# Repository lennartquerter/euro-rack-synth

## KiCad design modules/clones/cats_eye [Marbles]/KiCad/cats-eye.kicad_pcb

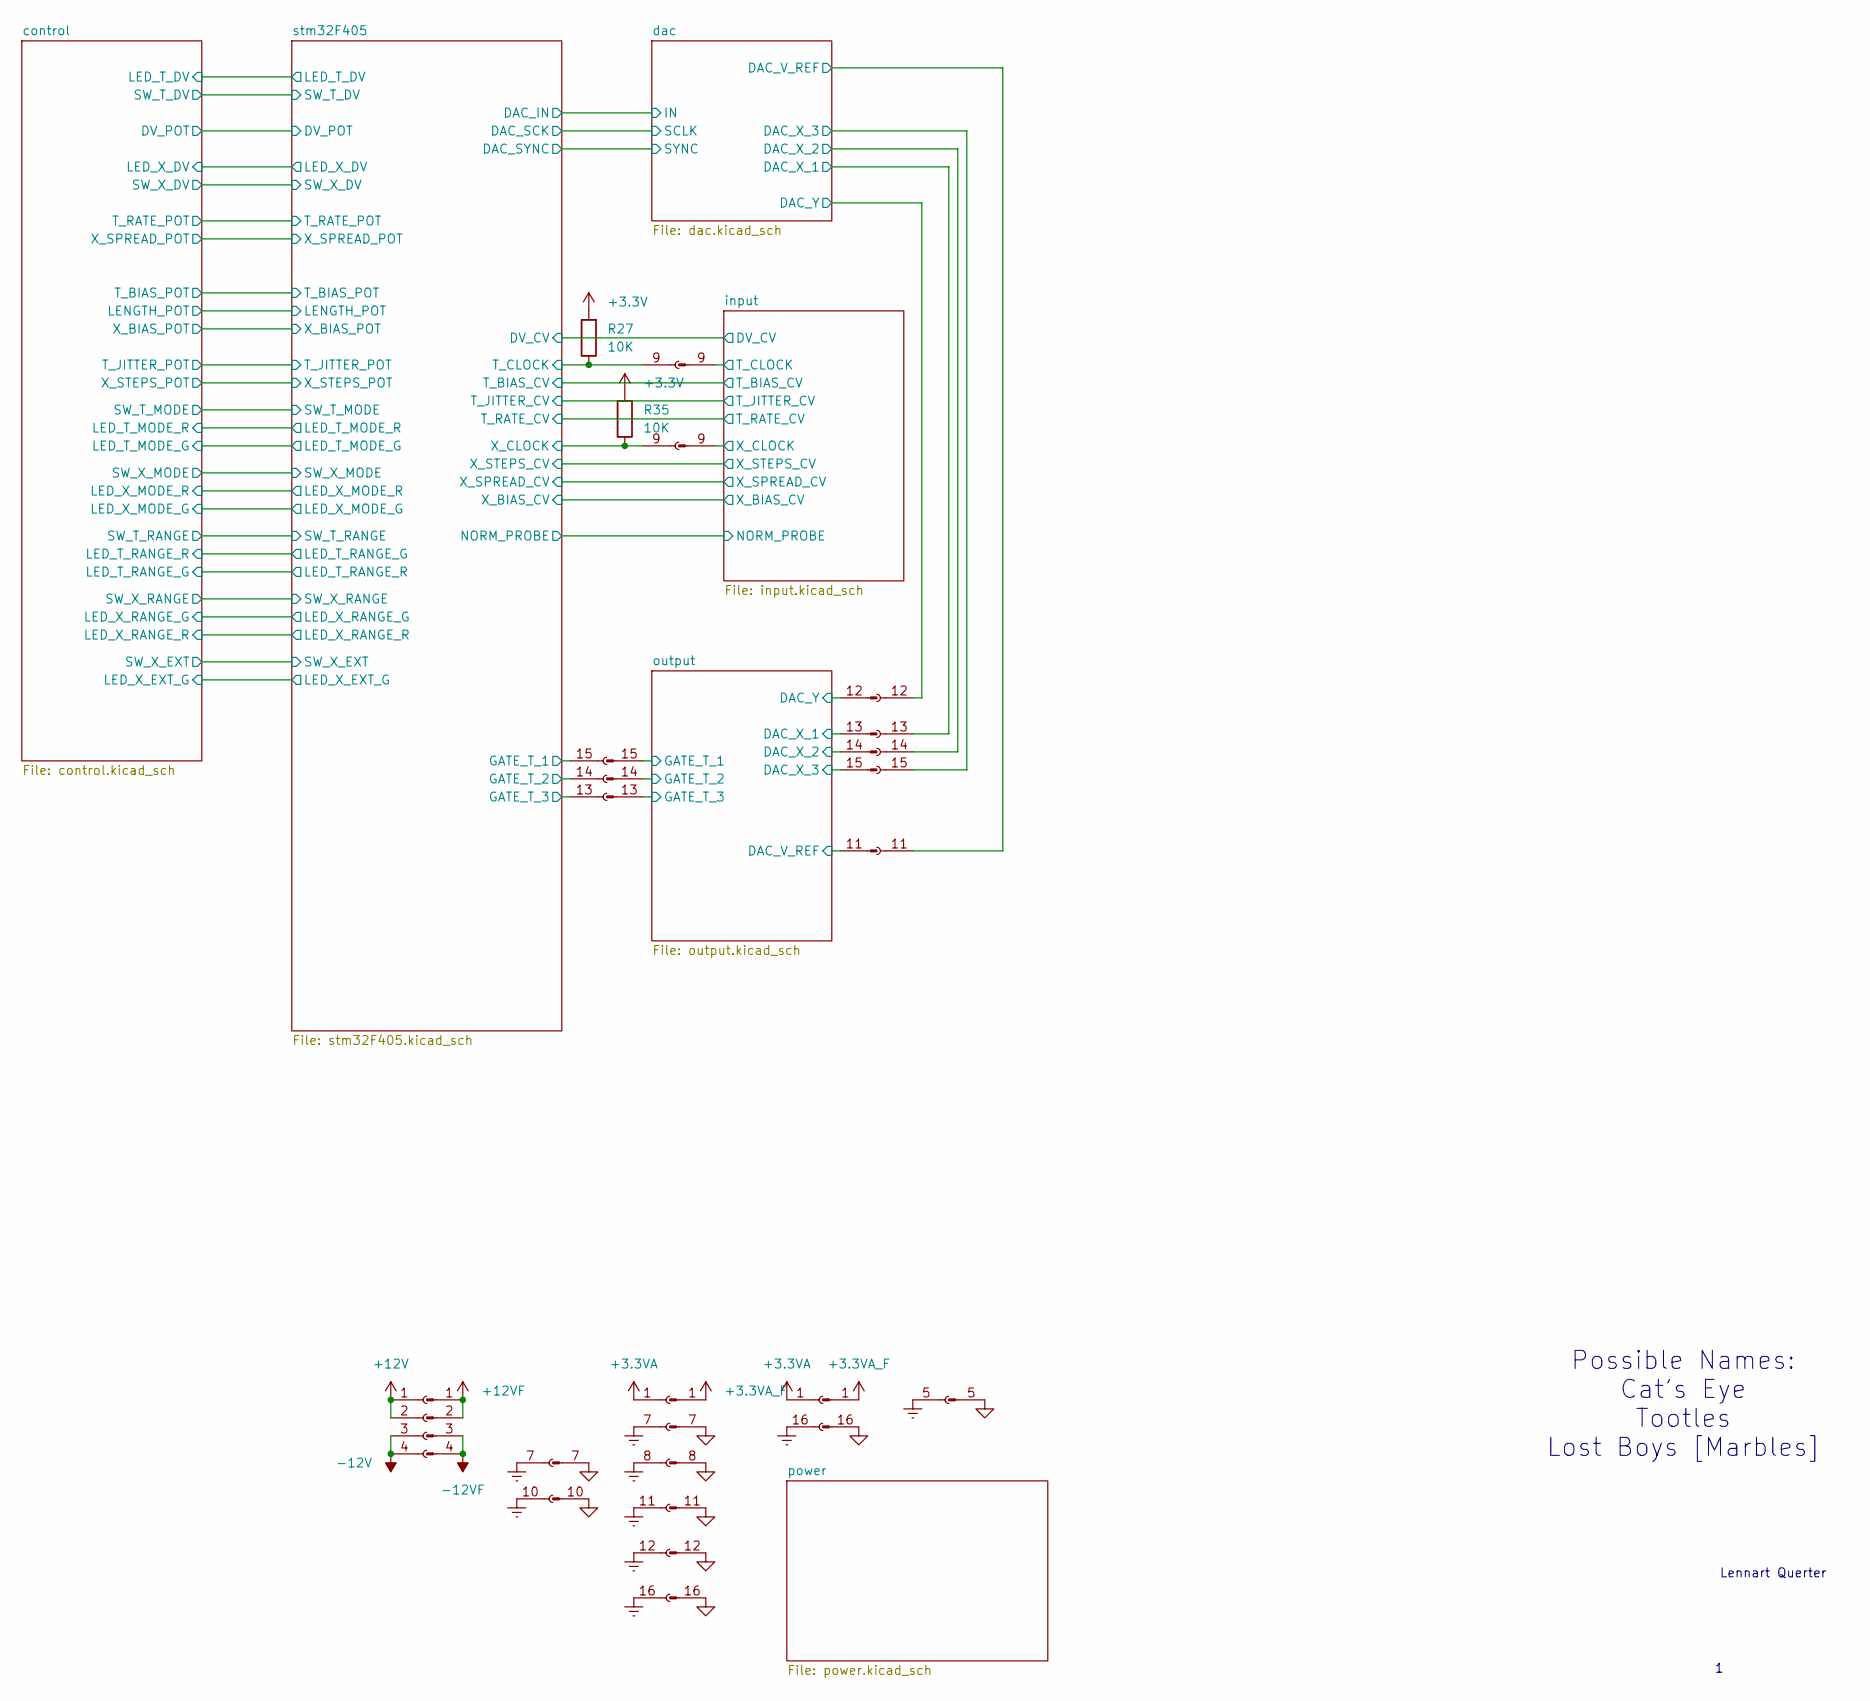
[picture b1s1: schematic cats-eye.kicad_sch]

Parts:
R27, R35: 10K; R_0805_2012Metric_Pad1.20x1.40mm_HandSolder
XP1, XP3, XP8: Conn_01x16_Socket; PinSocket_1x16_P2.54mm_Vertical
XP2, XP4, XP7: Conn_01x16_Pin; PinHeader_1x16_P2.54mm_Vertical
XP5: Conn_01x08_Socket; PinSocket_1x08_P2.54mm_Vertical
XP6: Conn_01x08_Pin; PinHeader_1x08_P2.54mm_Vertical
XP9: Conn_01x04_Pin; PinHeader_1x04_P2.54mm_Vertical
XP10: Conn_01x04_Socket; PinSocket_1x04_P2.54mm_Vertical

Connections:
+3.3V: R27.2, R35.2; also elsewhere on the board
+3.3VA: XP1.1, XP3.1; also elsewhere on the board
+3.3VA_F: XP2.1, XP4.1; also elsewhere on the board
+12V: XP10.1, XP10.2; also elsewhere on the board
+12VF: XP9.1, XP9.2; also elsewhere on the board
-12V: XP10.3, XP10.4; also elsewhere on the board
-12VF: XP9.3, XP9.4; also elsewhere on the board
/dac/DAC_V_REF: XP3.11; also elsewhere on the board
/dac/DAC_X_1: XP3.13; also elsewhere on the board
/dac/DAC_X_2: XP3.14; also elsewhere on the board
/dac/DAC_X_3: XP3.15; also elsewhere on the board
/dac/DAC_Y: XP3.12; also elsewhere on the board
/input/T_CLOCK: XP2.9; also elsewhere on the board
/input/X_CLOCK: XP4.9; also elsewhere on the board
/output/DAC_V_REF: XP4.11; also elsewhere on the board
/output/DAC_X_1: XP4.13; also elsewhere on the board
/output/DAC_X_2: XP4.14; also elsewhere on the board
/output/DAC_X_3: XP4.15; also elsewhere on the board
/output/DAC_Y: XP4.12; also elsewhere on the board
/output/GATE_T_1: XP2.15; also elsewhere on the board
/output/GATE_T_2: XP2.14; also elsewhere on the board
/output/GATE_T_3: XP2.13; also elsewhere on the board
/stm32F405/GATE_T_1: XP1.15; also elsewhere on the board
/stm32F405/GATE_T_2: XP1.14; also elsewhere on the board
/stm32F405/GATE_T_3: XP1.13; also elsewhere on the board
/stm32F405/T_CLOCK: R27.1, XP1.9; also elsewhere on the board
/stm32F405/X_CLOCK: R35.1, XP3.9; also elsewhere on the board
GND: XP2.7, XP2.8, XP2.11, XP2.12, XP2.16, XP4.16, XP6.5, XP7.7, XP7.10; also elsewhere on the board
GNDREF: XP1.7, XP1.8, XP1.11, XP1.12, XP1.16, XP3.16, XP5.5, XP8.7, XP8.10; also elsewhere on the board

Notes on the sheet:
Possible Names: Cat's Eye Tootles Lost Boys [Marbles]
Lennart Querter

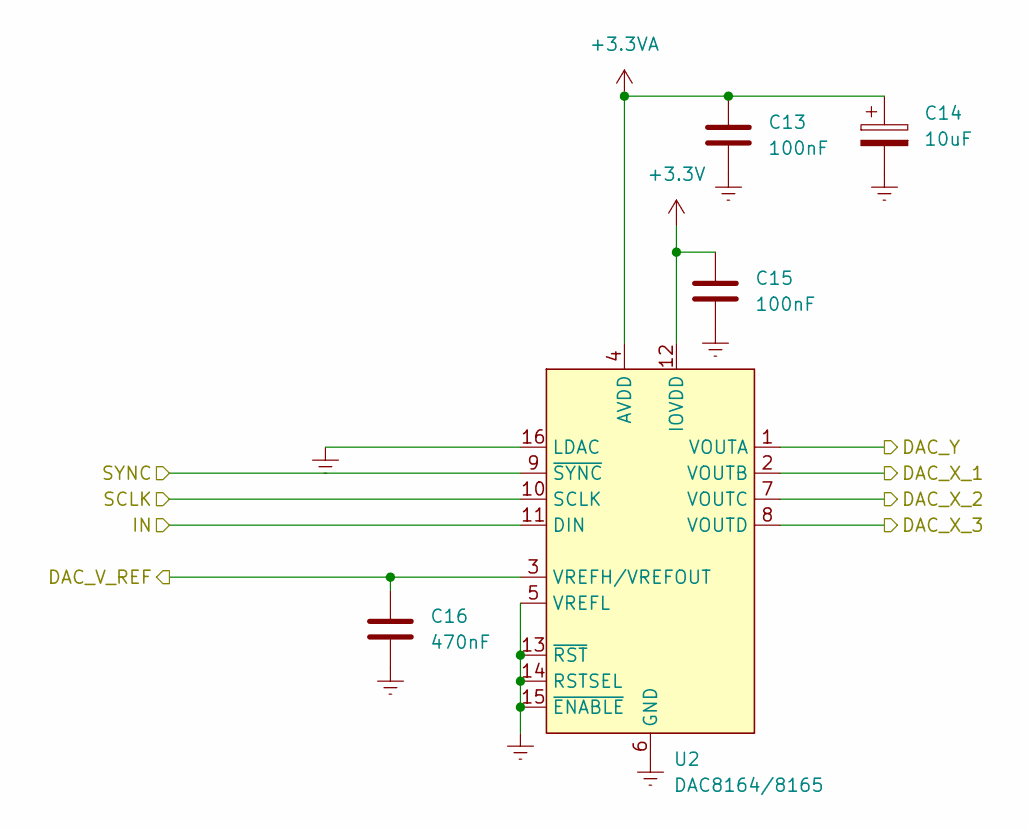
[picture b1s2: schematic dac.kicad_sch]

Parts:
C13, C15: 100nF; C_0805_2012Metric_Pad1.18x1.45mm_HandSolder
C14: 10uF; CP_Radial_D4.0mm_P2.00mm
C16: 470nF; C_0805_2012Metric_Pad1.18x1.45mm_HandSolder
U2: DAC8164/8165; TSSOP-16_4.4x5mm_P0.65mm

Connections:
+3.3V: C15.2, U2.12 (IOVDD); also elsewhere on the board
+3.3VA: C13.2, C14.1, U2.4 (AVDD); also elsewhere on the board
/dac/DAC_V_REF: C16.2, U2.3 (VREFH/VREFOUT); also elsewhere on the board
/dac/DAC_X_1: U2.2 (VOUTB); also elsewhere on the board
/dac/DAC_X_2: U2.7 (VOUTC); also elsewhere on the board
/dac/DAC_X_3: U2.8 (VOUTD); also elsewhere on the board
/dac/DAC_Y: U2.1 (VOUTA); also elsewhere on the board
/dac/IN: U2.11 (DIN); also elsewhere on the board
/dac/SCLK: U2.10 (SCLK); also elsewhere on the board
/dac/SYNC: U2.9 (~SYNC); also elsewhere on the board
GNDREF: C13.1, C14.2, C15.1, C16.1, U2.5 (VREFL), U2.6 (GND), U2.13 (~RST), U2.14 (RSTSEL), U2.15 (~ENABLE), U2.16 (LDAC); also elsewhere on the board

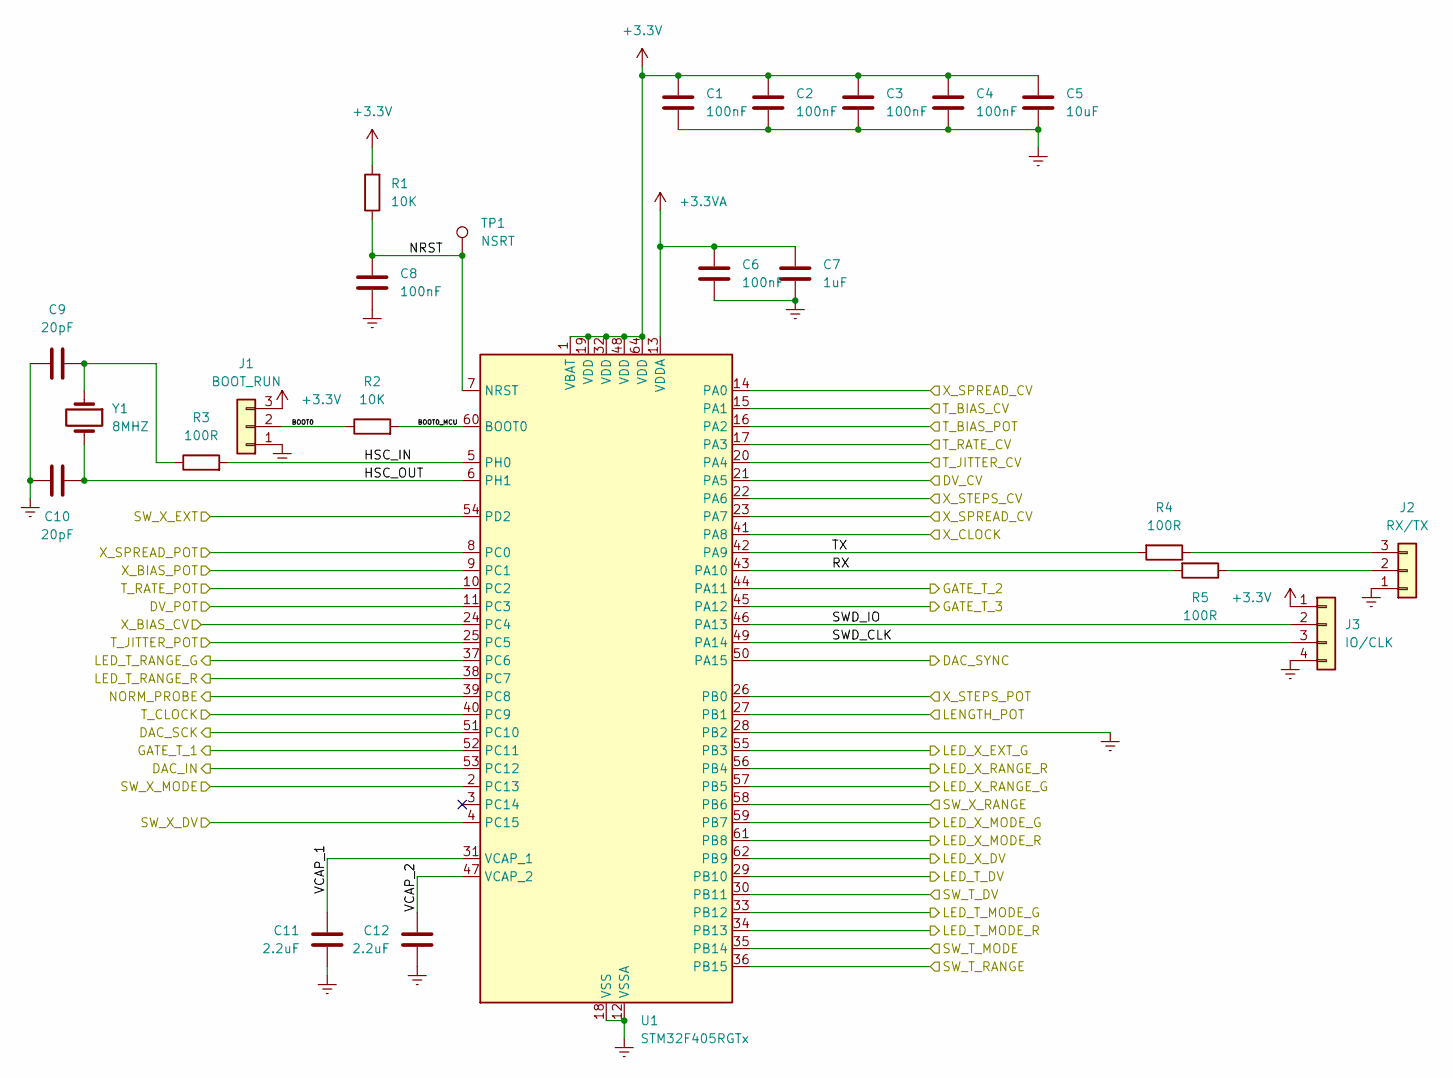
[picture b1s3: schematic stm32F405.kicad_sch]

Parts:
C1, C2, C3, C4, C6, C8: 100nF; C_0805_2012Metric_Pad1.18x1.45mm_HandSolder
C5: 10uF; C_0805_2012Metric_Pad1.18x1.45mm_HandSolder
C7: 1uF; C_0805_2012Metric_Pad1.18x1.45mm_HandSolder
C9, C10: 20pF; C_0805_2012Metric_Pad1.18x1.45mm_HandSolder
C11, C12: 2.2uF; C_0805_2012Metric_Pad1.18x1.45mm_HandSolder
J1: BOOT_RUN; PinHeader_1x03_P2.54mm_Vertical
J2: RX/TX; PinHeader_1x03_P2.54mm_Vertical
J3: IO/CLK; PinHeader_1x04_P2.54mm_Vertical
R1, R2: 10K; R_0805_2012Metric_Pad1.20x1.40mm_HandSolder
R3, R4, R5: 100R; R_0805_2012Metric_Pad1.20x1.40mm_HandSolder
TP1: NSRT; Pin_D1.0mm_L10.0mm
U1: STM32F405RGTx; LQFP-64_10x10mm_P0.5mm
Y1: 8MHZ; Crystal_SMD_HC49-SD_HandSoldering

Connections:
+3.3V: C1.2, C2.2, C3.2, C4.2, C5.2, J1.3, J3.1, R1.2, U1.1 (VBAT), U1.19 (VDD), U1.32 (VDD), U1.48 (VDD), U1.64 (VDD); also elsewhere on the board
+3.3VA: C6.2, C7.2, U1.13 (VDDA); also elsewhere on the board
/control/DV_POT: U1.11 (PC3); also elsewhere on the board
/control/LED_T_DV: U1.29 (PB10); also elsewhere on the board
/control/LED_T_MODE_G: U1.33 (PB12); also elsewhere on the board
/control/LED_T_MODE_R: U1.34 (PB13); also elsewhere on the board
/control/LED_T_RANGE_G: U1.38 (PC7); also elsewhere on the board
/control/LED_T_RANGE_R: U1.37 (PC6); also elsewhere on the board
/control/LED_X_DV: U1.62 (PB9); also elsewhere on the board
/control/LED_X_EXT_G: U1.55 (PB3); also elsewhere on the board
/control/LED_X_MODE_G: U1.59 (PB7); also elsewhere on the board
/control/LED_X_MODE_R: U1.61 (PB8); also elsewhere on the board
/control/LED_X_RANGE_G: U1.57 (PB5); also elsewhere on the board
/control/LED_X_RANGE_R: U1.56 (PB4); also elsewhere on the board
/control/LENGTH_POT: U1.27 (PB1); also elsewhere on the board
/control/SW_T_DV: U1.30 (PB11); also elsewhere on the board
/control/SW_T_MODE: U1.35 (PB14); also elsewhere on the board
/control/SW_T_RANGE: U1.36 (PB15); also elsewhere on the board
/control/SW_X_DV: U1.4 (PC15); also elsewhere on the board
/control/SW_X_EXT: U1.54 (PD2); also elsewhere on the board
/control/SW_X_MODE: U1.2 (PC13); also elsewhere on the board
/control/SW_X_RANGE: U1.58 (PB6); also elsewhere on the board
/control/T_BIAS_POT: U1.16 (PA2); also elsewhere on the board
/control/T_JITTER_POT: U1.25 (PC5); also elsewhere on the board
/control/T_RATE_POT: U1.10 (PC2); also elsewhere on the board
/control/X_BIAS_POT: U1.9 (PC1); also elsewhere on the board
/control/X_SPREAD_POT: U1.8 (PC0); also elsewhere on the board
/control/X_STEPS_POT: U1.26 (PB0); also elsewhere on the board
/dac/IN: U1.53 (PC12); also elsewhere on the board
/dac/SCLK: U1.51 (PC10); also elsewhere on the board
/dac/SYNC: U1.50 (PA15); also elsewhere on the board
/input/DV_CV: U1.21 (PA5); also elsewhere on the board
/input/NORM_PROBE: U1.39 (PC8); also elsewhere on the board
/input/T_BIAS_CV: U1.15 (PA1); also elsewhere on the board
/input/T_JITTER_CV: U1.20 (PA4); also elsewhere on the board
/input/T_RATE_CV: U1.17 (PA3); also elsewhere on the board
/input/X_BIAS_CV: U1.24 (PC4); also elsewhere on the board
/input/X_SPREAD_CV: U1.14 (PA0), U1.23 (PA7); also elsewhere on the board
/input/X_STEPS_CV: U1.22 (PA6); also elsewhere on the board
/stm32F405/BOOT0: J1.2, R2.1
/stm32F405/BOOT0_MCU: R2.2, U1.60 (BOOT0)
/stm32F405/GATE_T_1: U1.52 (PC11); also elsewhere on the board
/stm32F405/GATE_T_2: U1.44 (PA11); also elsewhere on the board
/stm32F405/GATE_T_3: U1.45 (PA12); also elsewhere on the board
/stm32F405/HSC_IN: R3.2, U1.5 (PH0)
/stm32F405/HSC_OUT: C10.1, U1.6 (PH1), Y1.2
/stm32F405/NRST: C8.1, R1.1, TP1.1, U1.7 (NRST)
/stm32F405/RX: R5.2, U1.43 (PA10)
/stm32F405/SWD_CLK: J3.3, U1.49 (PA14)
/stm32F405/SWD_IO: J3.2, U1.46 (PA13)
/stm32F405/TX: R4.2, U1.42 (PA9)
/stm32F405/T_CLOCK: U1.40 (PC9); also elsewhere on the board
/stm32F405/VCAP_1: C11.1, U1.31 (VCAP_1)
/stm32F405/VCAP_2: C12.1, U1.47 (VCAP_2)
/stm32F405/X_CLOCK: U1.41 (PA8); also elsewhere on the board
GNDREF: C1.1, C2.1, C3.1, C4.1, C5.1, C6.1, C7.1, C8.2, C9.2, C10.2, C11.2, C12.2, J1.1, J2.1, J3.4, U1.12 (VSSA), U1.18 (VSS), U1.28 (PB2), U1.63 (VSS); also elsewhere on the board
unnamed: C9.1, R3.1, Y1.1
unnamed: J2.2, R5.1
unnamed: J2.3, R4.1

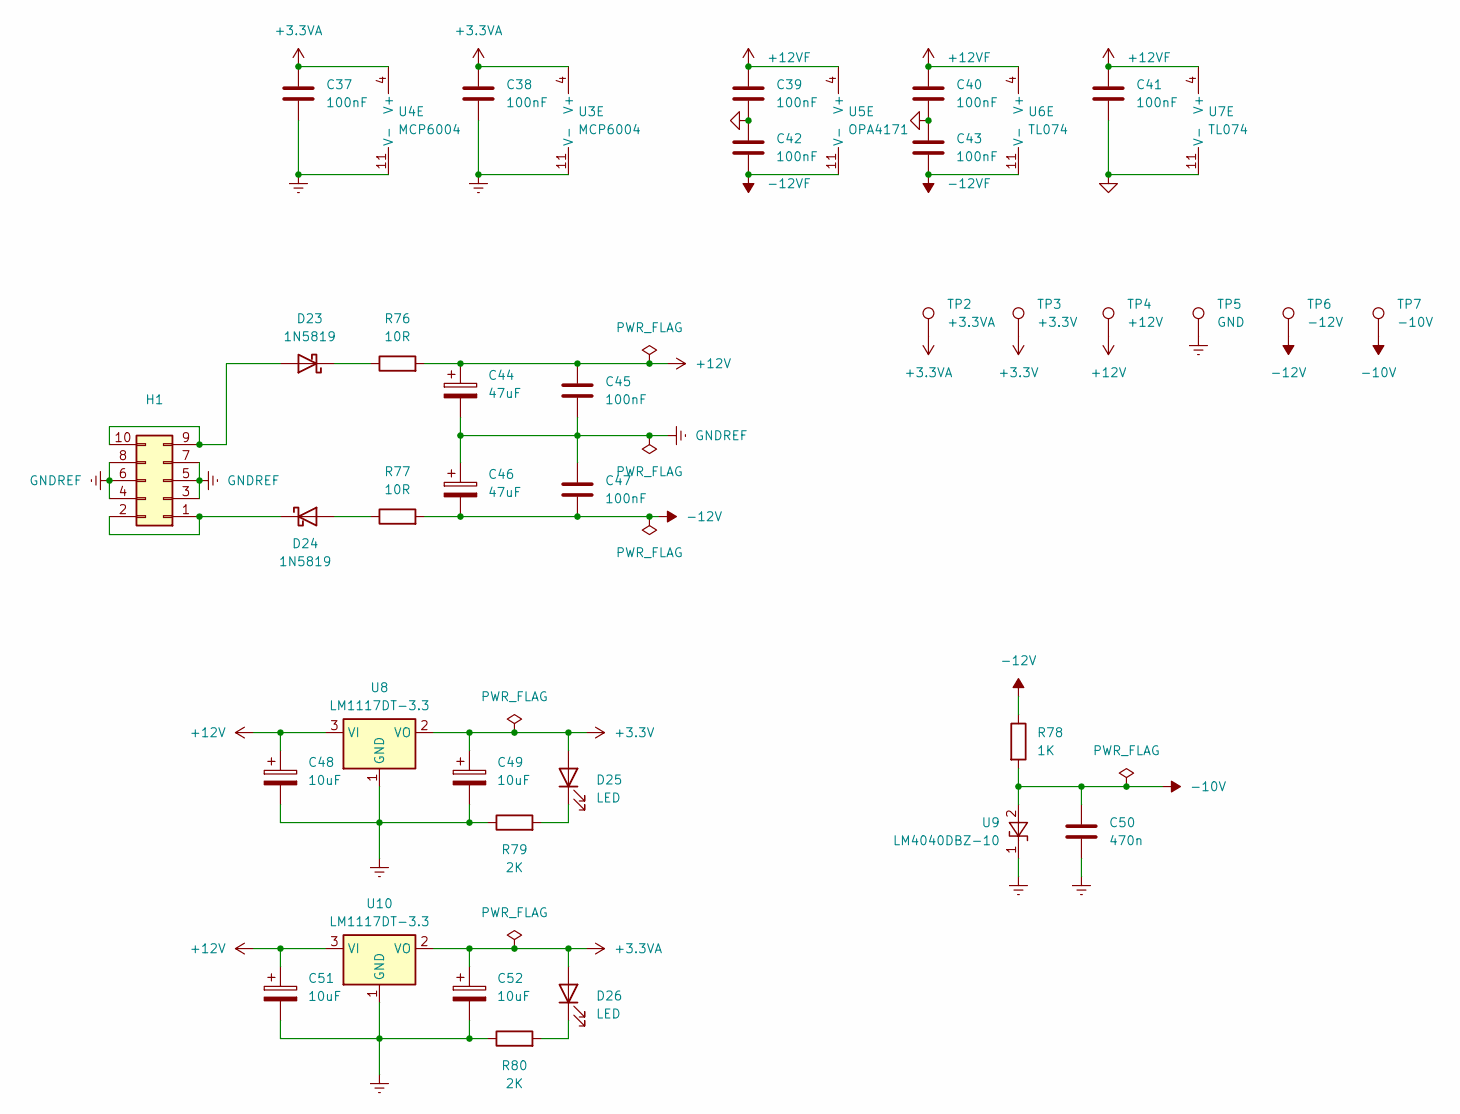
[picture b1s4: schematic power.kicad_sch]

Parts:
C37, C38, C39, C40, C41, C42, C43, C45, C47: 100nF; C_0805_2012Metric_Pad1.18x1.45mm_HandSolder
C44, C46: 47uF; CP_Radial_D5.0mm_P2.50mm
C48, C49, C51, C52: 10uF; CP_Radial_D4.0mm_P2.00mm
C50: 470n; C_0805_2012Metric_Pad1.18x1.45mm_HandSolder
D23, D24: 1N5819; D_SOD-123
D25, D26: LED; LED_0805_2012Metric_Pad1.15x1.40mm_HandSolder
H1: Conn_02x05_PWR_Eurorack; IDC-Header_2x05_P2.54mm_Vertical
R76, R77: 10R; R_0805_2012Metric_Pad1.20x1.40mm_HandSolder
R78: 1K; R_0805_2012Metric_Pad1.20x1.40mm_HandSolder
R79, R80: 2K; R_0805_2012Metric_Pad1.20x1.40mm_HandSolder
TP2: +3.3VA; Pin_D1.0mm_L10.0mm
TP3: +3.3V; Pin_D1.0mm_L10.0mm
TP4: +12V; Pin_D1.0mm_L10.0mm
TP5: GND; Pin_D1.0mm_L10.0mm
TP6: -12V; Pin_D1.0mm_L10.0mm
TP7: -10V; Pin_D1.0mm_L10.0mm
U3, U4: MCP6004; SOIC-14
U5: OPA4171; SOIC-14
U6, U7: TL074; SOIC-14
U8, U10: LM1117DT-3.3; TO-252-3_TabPin2
U9: LM4040DBZ-10; SOT-23

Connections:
+3.3V: C49.1, D25.2 (A), TP3.1, U8.2 (VO); also elsewhere on the board
+3.3VA: C37.1, C38.1, C52.1, D26.2 (A), TP2.1, U3.4 (V+), U4.4 (V+), U10.2 (VO); also elsewhere on the board
+12V: C44.1, C45.1, C48.1, C51.1, R76.2, TP4.1, U8.3 (VI), U10.3 (VI); also elsewhere on the board
+12VF: C39.1, C40.1, C41.1, U5.4 (V+), U6.4 (V+), U7.4 (V+); also elsewhere on the board
-10V: C50.2, R78.2, TP7.1, U9.2 (A); also elsewhere on the board
-12V: C46.2, C47.2, R77.2, R78.1, TP6.1; also elsewhere on the board
-12VF: C42.2, C43.2, U5.11 (V-), U6.11 (V-); also elsewhere on the board
GND: C39.2, C40.2, C41.2, C42.1, C43.1, U7.11 (V-); also elsewhere on the board
GNDREF: C37.2, C38.2, C44.2, C45.2, C46.1, C47.1, C48.2, C49.2, C50.1, C51.2, C52.2, H1.3, H1.4, H1.5, H1.6, H1.7, H1.8, R79.1, R80.1, TP5.1, U3.11 (V-), U4.11 (V-), U8.1 (GND), U9.1 (K), U10.1 (GND); also elsewhere on the board
unnamed: D23.2 (A), H1.9, H1.10
unnamed: D23.1 (K), R76.1
unnamed: D24.2 (A), R77.1
unnamed: D24.1 (K), H1.1, H1.2
unnamed: D25.1 (K), R79.2
unnamed: D26.1 (K), R80.2

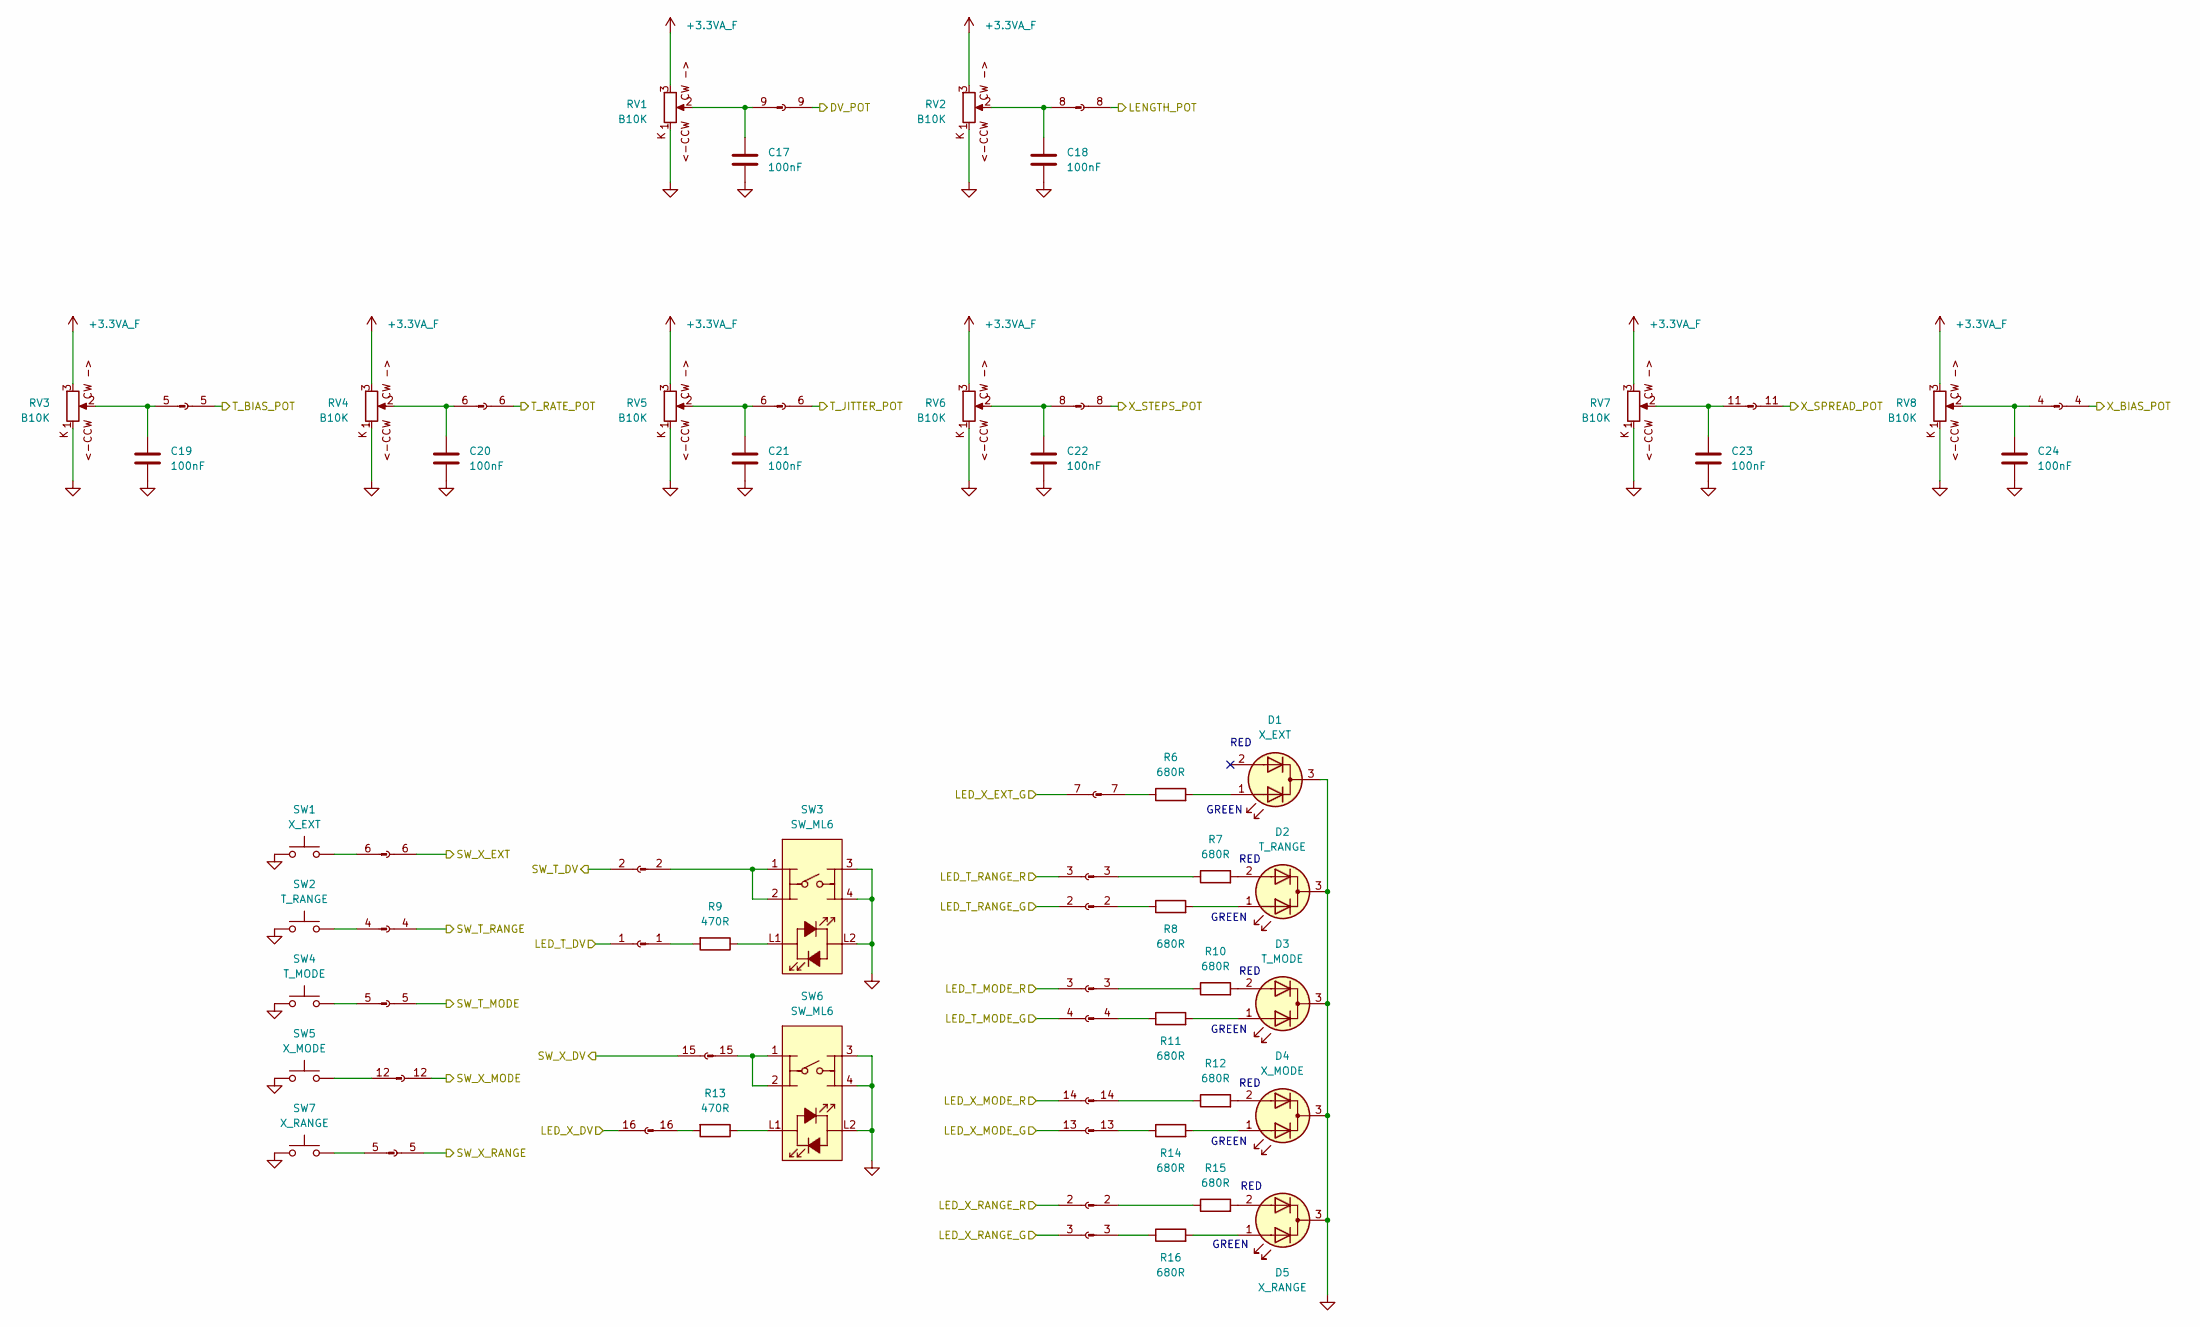
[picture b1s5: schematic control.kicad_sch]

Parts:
C17, C18, C19, C20, C21, C22, C23, C24: 100nF; C_0805_2012Metric_Pad1.18x1.45mm_HandSolder
D1: X_EXT; LED_D3.0mm-3_Dual
D2: T_RANGE; LED_D3.0mm-3_Dual_SM
D3: T_MODE; LED_D3.0mm-3_Dual
D4: X_MODE; LED_D3.0mm-3_Dual
D5: X_RANGE; LED_D3.0mm-3_Dual_SM
R6, R7, R8, R10, R11, R12, R14, R15, R16: 680R; R_0805_2012Metric_Pad1.20x1.40mm_HandSolder
R9, R13: 470R; R_0805_2012Metric_Pad1.20x1.40mm_HandSolder
RV1, RV2, RV3, RV4, RV5, RV6, RV7, RV8: B10K; Potentiometer_TT_P0915N
SW1: X_EXT; SW_PUSH_6mm
SW2: T_RANGE; SW_PUSH_6mm
SW3, SW6: SW_ML6; ML6-H2T2GQA
SW4: T_MODE; SW_PUSH_6mm
SW5: X_MODE; SW_PUSH_6mm
SW7: X_RANGE; SW_PUSH_6mm
XP1, XP3, XP8: Conn_01x16_Socket; PinSocket_1x16_P2.54mm_Vertical
XP2, XP4, XP7: Conn_01x16_Pin; PinHeader_1x16_P2.54mm_Vertical

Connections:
+3.3VA_F: RV1.3, RV2.3, RV3.3, RV4.3, RV5.3, RV6.3, RV7.3, RV8.3; also elsewhere on the board
/control/DV_POT: XP8.9; also elsewhere on the board
/control/LED_T_DV: XP8.1; also elsewhere on the board
/control/LED_T_MODE_G: XP8.4; also elsewhere on the board
/control/LED_T_MODE_R: XP8.3; also elsewhere on the board
/control/LED_T_RANGE_G: XP1.2; also elsewhere on the board
/control/LED_T_RANGE_R: XP1.3; also elsewhere on the board
/control/LED_X_DV: XP8.16; also elsewhere on the board
/control/LED_X_EXT_G: XP3.7; also elsewhere on the board
/control/LED_X_MODE_G: XP8.13; also elsewhere on the board
/control/LED_X_MODE_R: XP8.14; also elsewhere on the board
/control/LED_X_RANGE_G: XP3.3; also elsewhere on the board
/control/LED_X_RANGE_R: XP3.2; also elsewhere on the board
/control/LENGTH_POT: XP8.8; also elsewhere on the board
/control/SW_T_DV: XP8.2; also elsewhere on the board
/control/SW_T_MODE: XP8.5; also elsewhere on the board
/control/SW_T_RANGE: XP1.4; also elsewhere on the board
/control/SW_X_DV: XP8.15; also elsewhere on the board
/control/SW_X_EXT: XP3.6; also elsewhere on the board
/control/SW_X_MODE: XP8.12; also elsewhere on the board
/control/SW_X_RANGE: XP3.5; also elsewhere on the board
/control/T_BIAS_POT: XP1.5; also elsewhere on the board
/control/T_JITTER_POT: XP1.6; also elsewhere on the board
/control/T_RATE_POT: XP8.6; also elsewhere on the board
/control/X_BIAS_POT: XP3.4; also elsewhere on the board
/control/X_SPREAD_POT: XP8.11; also elsewhere on the board
/control/X_STEPS_POT: XP3.8; also elsewhere on the board
GND: C17.1, C18.1, C19.1, C20.1, C21.1, C22.1, C23.1, C24.1, D1.3 (K), D2.3 (K), D3.3 (K), D4.3 (K), D5.3 (K), RV1.1, RV2.1, RV3.1, RV4.1, RV5.1, RV6.1, RV7.1, RV8.1, SW1.1, SW2.1, SW3.3, SW3.4 (A), SW3.L2, SW4.1, SW5.1, SW6.3, SW6.4 (A), SW6.L2, SW7.1; also elsewhere on the board
unnamed: D1.1 (A1), R6.2
unnamed: D2.1 (A1), R8.2
unnamed: D2.2 (A2), R7.2
unnamed: D3.1 (A1), R11.2
unnamed: D3.2 (A2), R10.2
unnamed: D4.1 (A1), R14.2
unnamed: D4.2 (A2), R12.2
unnamed: D5.1 (A1), R16.2
unnamed: D5.2 (A2), R15.2
unnamed: R9.1, SW3.L1
unnamed: R13.1, SW6.L1
unnamed: R8.1, XP2.2
unnamed: R7.1, XP2.3
unnamed: SW2.2, XP2.4
unnamed: C19.2, RV3.2, XP2.5
unnamed: C21.2, RV5.2, XP2.6
unnamed: R15.1, XP4.2
unnamed: R16.1, XP4.3
unnamed: C24.2, RV8.2, XP4.4
unnamed: SW7.2, XP4.5
unnamed: SW1.2, XP4.6
unnamed: R6.1, XP4.7
unnamed: C22.2, RV6.2, XP4.8
unnamed: R9.2, XP7.1
unnamed: SW3.1, SW3.2, XP7.2
unnamed: R10.1, XP7.3
unnamed: R11.1, XP7.4
unnamed: SW4.2, XP7.5
unnamed: C20.2, RV4.2, XP7.6
unnamed: C18.2, RV2.2, XP7.8
unnamed: C17.2, RV1.2, XP7.9
unnamed: C23.2, RV7.2, XP7.11
unnamed: SW5.2, XP7.12
unnamed: R14.1, XP7.13
unnamed: R12.1, XP7.14
unnamed: SW6.1, SW6.2, XP7.15
unnamed: R13.2, XP7.16

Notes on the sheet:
GREEN
RED

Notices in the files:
modules/clones/cats_eye [Marbles]/KiCad/cats-eye.kicad_pcb:
cc-by-sa
modules/clones/wolkje/KiCad/wolkje.kicad_pcb:
cc-by-sa - Emilie Gillet
